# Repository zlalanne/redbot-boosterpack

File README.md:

# RedBot BoosterPack

This project is a port of Sparkfun's RedBot Mainboard to BoosterPack form to be used with TI LaunchPads + Energia

Please check the GitHub issue tracker for any known hardware/software issues

## Changes from SparkFun's RedBot Mainboard
* Removed Atmega328 and replaced with BoosterPack headers. BoosterPack should work with any 40-pin launchpad that follows the [BoosterPack pinout standard](http://www.ti.com/ww/en/launchpad/img/launchpad-byob-pinout.png)
* Removed XBee to make board cheaper, if XBee needed get another BoosterPack
* Made sizes of caps/resistors larger to make soldering easier
* Most of the logic now runs on 3.3V since the F5529 is 3.3V as well
* Removed USB connection that was using for programming device, programming is handled on the LaunchPad
* Changed layout from 4 layer to 2 layer

## Additional Hardware Support
One of the great features about the RedBot ecosystem is the number of products SparkFun has come out with that plug into the RedBot. 

The following are currently fully supported:
* [Magician Chasis (including motors)](https://www.sparkfun.com/products/10825)
* [RedBot Buzzer](https://www.sparkfun.com/products/12567)
* [RedBot Sensor - Mechanical Bumper](https://www.sparkfun.com/products/11999). Need to put instructions on wiki

The following are under development
* [RedBot Sensor - Line Follower](https://www.sparkfun.com/products/11769). Needs software support
* [RedBot Sensor - Wheel Encoder](https://www.sparkfun.com/products/12617). Needs software support
* [RedBot Sensor - Accelerometer](https://www.sparkfun.com/products/12589). Issue with v1.0 of board, needs software support

## Repository Contents
* **/Firmware/RedBot** - RedBot Energia library
* **/Hardware** - Eagle PCB layout and schematic files along with BOM

## License Information
License is inherited from [SparkFun's RedBot repository](https://github.com/sparkfun/RedBot)

All contents of this repository are released under [Creative Commons Share-alike 3.0](http://creativecommons.org/licenses/by-sa/3.0/).

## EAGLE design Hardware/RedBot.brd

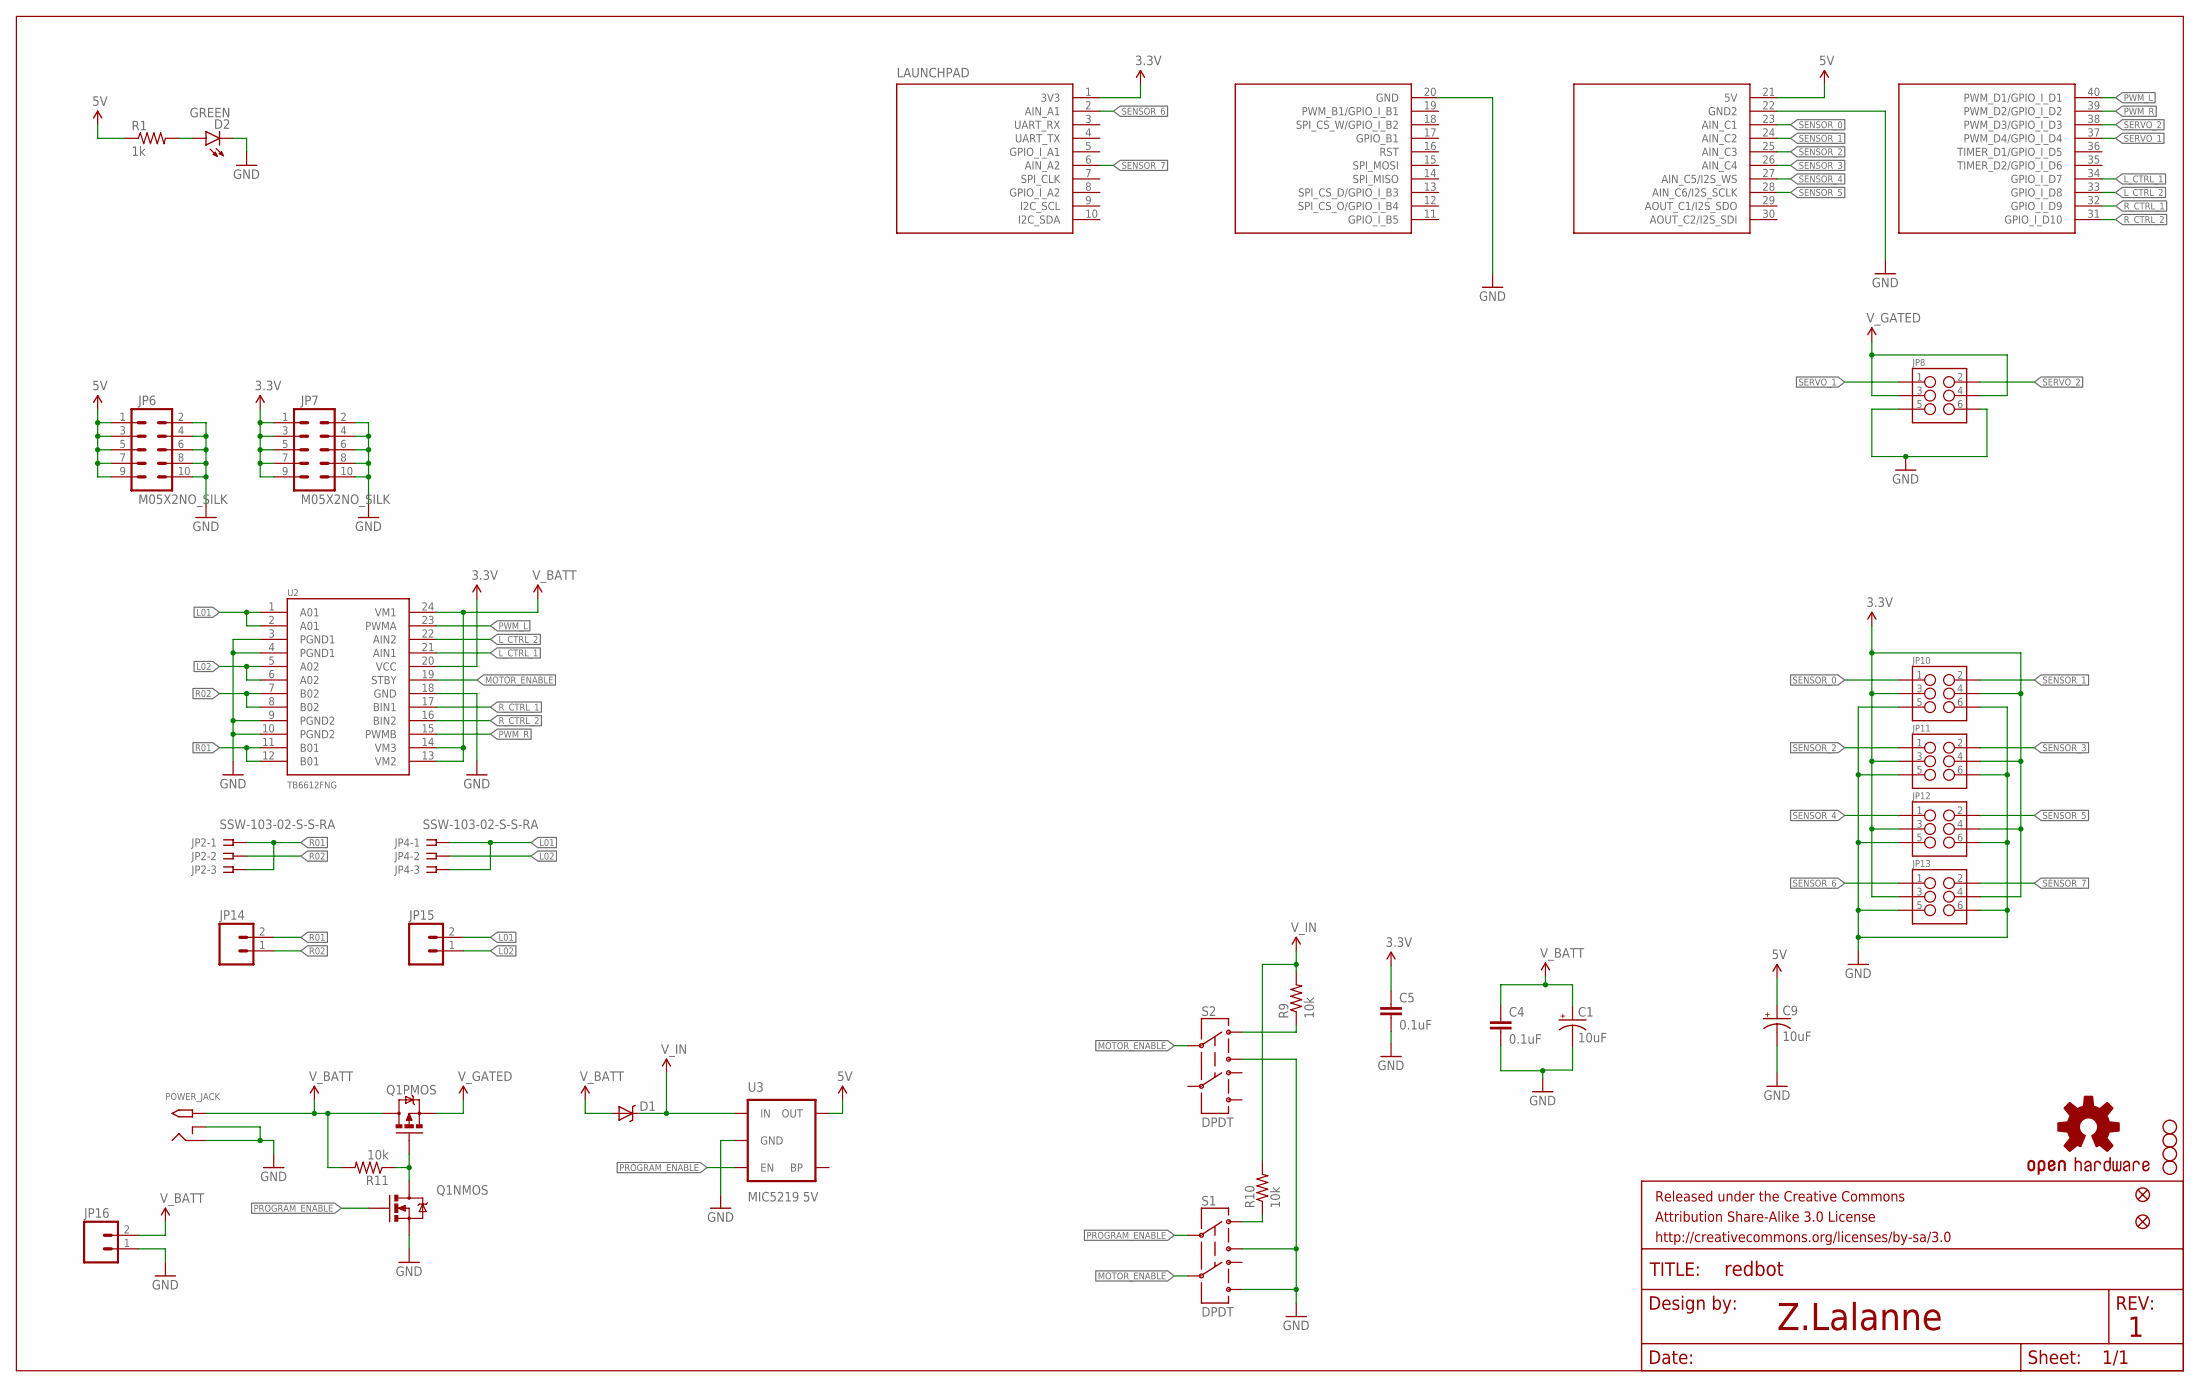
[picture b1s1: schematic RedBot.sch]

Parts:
C1, C9: 10uF; EIA3216
C4, C5: 0.1uF; 1206
D1: B340A; SMA-DIODE
D2: GREEN; LED-1206
FID1, FID2: FIDUCIALUFIDUCIAL; MICRO-FIDUCIAL
FRAME1: FRAME-LETTER; CREATIVE_COMMONS
JP2, JP4: SSW-103-02-S-S-RA
JP6, JP7: M05X2NO_SILK; 2X5_NOSILK
JP8, JP10, JP11, JP12, JP13: M03X22X3_SILK_SM; 2X3
JP14, JP15, JP16: M02PTH; 1X02
LAUNCHPAD: BOOSTERPACK; BOOSTERPACK40
POWER_JACK: 2.1MMJACKTHM; PJ-102A
Q1: IRF7509; MSOP8
R1: 1k; 1206
R9, R10, R11: 10k; 1206
S1, S2: DPDT; AYZ0202
STANDOFF1, STANDOFF2, STANDOFF3, STANDOFF4: STAND-OFF
U2: TB6612FNG; SSOP24
U3: MIC5219 5V; SOT23-5
U$17: OSHW-LOGOS; OSHW-LOGO-S

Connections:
3.3V: C5.1, JP7.1, JP7.3, JP7.5, JP7.7, JP7.9, JP10.3, JP10.4, JP11.3, JP11.4, JP12.3, JP12.4, JP13.3, JP13.4, LAUNCHPAD.1 (3V3), U2.20 (VCC)
5V: C9.A (+), JP6.1, JP6.3, JP6.5, JP6.7, JP6.9, LAUNCHPAD.21 (5V), R1.1, U3.5 (OUT)
GND: C1.C (-), C4.2, C5.2, C9.C (-), D2.C, JP6.2, JP6.4, JP6.6, JP6.8, JP6.10, JP7.2, JP7.4, JP7.6, JP7.8, JP7.10, JP8.5, JP8.6, JP10.5, JP10.6, JP11.5, JP11.6, JP12.5, JP12.6, JP13.5, JP13.6, JP16.1, LAUNCHPAD.20 (GND), LAUNCHPAD.22 (GND2), POWER_JACK.RING, POWER_JACK.RING_SW, Q1.1 (S), S1.3, S1.6, S2.3, U2.3 (PGND1), U2.4 (PGND1), U2.9 (PGND2), U2.10 (PGND2), U2.18 (GND), U3.2 (GND)
L01: JP4.1, JP4.3, JP15.2, U2.1 (A01), U2.2 (A01)
L02: JP4.2, JP15.1, U2.5 (A02), U2.6 (A02)
L_CTRL_1: LAUNCHPAD.34 (GPIO_I_D7), U2.21 (AIN1)
L_CTRL_2: LAUNCHPAD.33 (GPIO_I_D8), U2.22 (AIN2)
MOTOR_ENABLE: S1.5, S2.2, U2.19 (STBY)
unnamed: D2.A, R1.2
unnamed: Q1.4 (G), Q1.7 (D), Q1.8 (D), R11.1
unnamed: R9.1, S2.1
PG_EN: R10.1, S1.1
PROGRAM_ENABLE: Q1.2 (G), S1.2, U3.3 (EN)
PWM_L: LAUNCHPAD.40 (PWM_D1/GPIO_I_D1), U2.23 (PWMA)
PWM_R: LAUNCHPAD.39 (PWM_D2/GPIO_I_D2), U2.15 (PWMB)
R01: JP2.1, JP2.3, JP14.2, U2.11 (B01), U2.12 (B01)
R02: JP2.2, JP14.1, U2.7 (B02), U2.8 (B02)
R_CTRL_1: LAUNCHPAD.32 (GPIO_I_D9), U2.17 (BIN1)
R_CTRL_2: LAUNCHPAD.31 (GPIO_I_D10), U2.16 (BIN2)
SENSOR_0: JP10.1, LAUNCHPAD.23 (AIN_C1)
SENSOR_1: JP10.2, LAUNCHPAD.24 (AIN_C2)
SENSOR_2: JP11.1, LAUNCHPAD.25 (AIN_C3)
SENSOR_3: JP11.2, LAUNCHPAD.26 (AIN_C4)
SENSOR_4: JP12.1, LAUNCHPAD.27 (AIN_C5/I2S_WS)
SENSOR_5: JP12.2, LAUNCHPAD.28 (AIN_C6/I2S_SCLK)
SENSOR_6: JP13.1, LAUNCHPAD.2 (AIN_A1)
SENSOR_7: JP13.2, LAUNCHPAD.6 (AIN_A2)
SERVO_1: JP8.1, LAUNCHPAD.37 (PWM_D4/GPIO_I_D4)
SERVO_2: JP8.2, LAUNCHPAD.38 (PWM_D3/GPIO_I_D3)
V_BATT: C1.A (+), C4.1, D1.A, JP16.2, POWER_JACK.TIP, Q1.5 (D), Q1.6 (D), R11.2, U2.13 (VM2), U2.14 (VM3), U2.24 (VM1)
V_GATED: JP8.3, JP8.4, Q1.3 (S)
V_IN: D1.C, R9.2, R10.2, U3.1 (IN)

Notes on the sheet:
Z.Lalanne

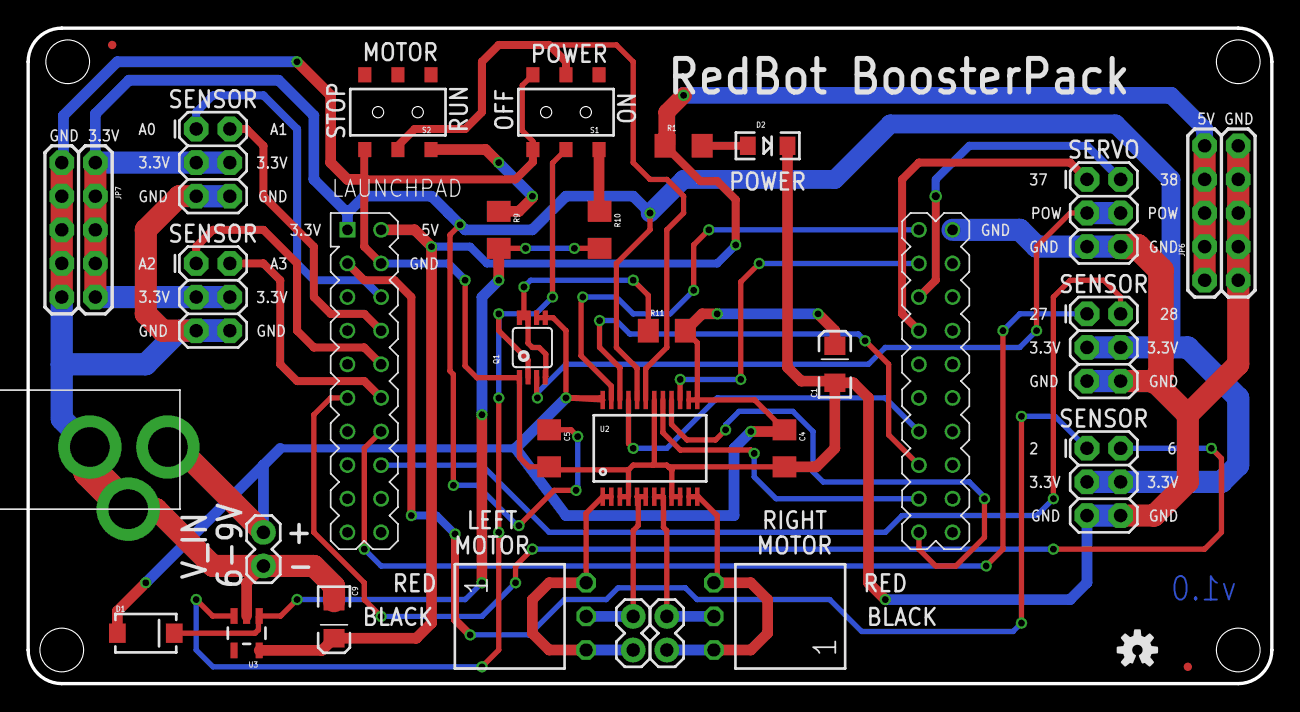
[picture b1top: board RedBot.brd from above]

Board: 2 copper layers, 94.0 x 49.5 mm, 37 parts (0 on the bottom side), 32 nets.

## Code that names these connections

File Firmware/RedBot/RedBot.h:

/****************************************************************
Core header file for all the various RedBot functions.

There is additional license info below regarding the use of the
SoftwareSerial library from Arduino 1.0.5; I had good and sound
reasons for creating a derivative class rather than asking users
to simply use the existing library, which are documented below.

This code is beerware; if you use it, please buy me (or any other
SparkFun employee) a cold beverage next time you run into one of
us at the local.

21 Jan 2014- Mike Hord, SparkFun Electronics

Code developed in Arduino 1.0.5, on an SparkFun Redbot v12.
****************************************************************/
/****************************************************************
Migrated to Energia by Zack Lalanne
****************************************************************/

#ifndef RedBot_h
#define RedBot_h

#include <Energia.h>

// Pin aliases for the motor controller.
#define    L_CTRL_1   34
#define    L_CTRL_2   33
#define    PWM_L      40

#define    R_CTRL_1   32
#define    R_CTRL_2   31
#define    PWM_R      39

// PCINT functionality aliases. Each PCINT has a value set up when the
//  class member gets created, and the PCINT service routine will handle
//  the choosing the appropriate response to the interrupt.
#define NOT_IN_USE    0
#define WHISKER       1
#define LENCODER      2
#define RENCODER      3
#define SW_SERIAL     4

#define PCINT_A0      0
#define PCINT_A1      1
#define PCINT_A2      2
#define PCINT_A3      3
#define PCINT_A4      4
#define PCINT_A5      5
#define PCINT_3       6
#define PCINT_9       7
#define PCINT_10      8
#define PCINT_11      9

enum WHEEL {LEFT, RIGHT, BOTH}; // Variable for which wheel you're interested in
                  //  when you do things in the encoder class.

// These three functions need to work from within multiple classes, so we keep
//  them separate and add them as friend functions where appropriate.
void setPinChangeInterrupt(int pin, byte role); // The "role" of each pin is
                  //  stored in an array which is accessed in the interrupt
                  //  handler to determine what should be done on a falling edge
                  //  PC interrupt.
void pinFunctionHandler(byte pinIndex); // This is the function which actually
                  //  handles the legwork after the interrupt has identified
                  //  which pin caught the interrupt.
void brake(void); // Globally accessible motor brake. I couldn't figure out how
                  //  to set a function pointer to the RedBotMotor class
                  //  function, and it's a small function, so I just made a
                  //  global in the library.
void PC0Handler(byte PBTemp);
void PC1Handler(byte PCTemp);
void PC2Handler(byte PDTemp);


// This class handles motor functionality. I expect one instance of this at the
//  start of a piece of RedBot code.
class RedBotMotor
{
  public:
    RedBotMotor();          // Constructor. Mainly sets up pins.
    void drive(int speed);  // Drive in direction given by sign, at speed given
                            //  by magnitude of the parameter.
    void pivot(int speed);  // Pivot more or less in place. Turns motors in
                            //  opposite directions. Positive values correspond
                            //  to anti-clockwise rotation.
    void rightDrive(int speed); // Drive just the left motor, as drive().
    void leftDrive(int speed);  // Drive just the right motor, as drive().
    void stop();            // Stop motors, but allow them to coast to a halt.
    void brake();           // Quick-stop the motors, shorting the leads.
    void rightStop();       // Stop right motor, as with stop().
    void leftStop();        // Stop left motor, as with stop().
    void leftBrake();       // Quick-stop left motor, as with brake().
    void rightBrake();      // Quick-stop right motor, as with brake().
  private:
    void leftFwd(byte speed); // These functions are pretty self-explanatory,
    void leftRev(byte speed); //  and are called by the above functions once
    void rightFwd(byte speed);//  sign has been used to determine direction.
    void rightRev(byte speed);
};

// This handles the physical wire-whisker type bumper.
class RedBotBumper
{
  public:
    RedBotBumper(int pin); // Simple constructor; when the bumper gets hit, the
                           //  motors will stop.
    RedBotBumper(int pin, void(*functionPointer)(void)); // If the user wishes
                           //  to do something other than stop on a whisker,
                           //  bump, they can write a function to do so, and
                           //  use this constructor.
    int pressed();        // Check if bumper is pressed
  private:
    int pin;
    void setBumpFunction(int pin, void(*functionPointer)(void));
};


#endif

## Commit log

2014-03-20 Initial import of redbot schematic/board
2014-03-25 First pass at converting schematic
2014-03-25 Updated motor ic to use 3.3V
2014-03-26 Updated parts to use through hole for sensor/servo connectors
2014-05-06 Updated board and schematic
2014-05-21 Updated board with new power jack. Started routing. Added BOM
2014-05-21 Added gitignore for temp files
2014-05-21 Removing temporary files from git
2014-05-23 Updated all parts to be larger
2014-05-23 Finished layout of RedBot
2014-05-25 Finished silk on board
2014-05-29 Added bom in csv format
2014-05-29 Removed old bom
2014-06-14 Working motors in Energia
2014-06-14 Adding some examples
2014-06-14 Added example showing how to pivot
2014-06-14 Added comments to mention port to energia
2014-06-14 Updated readme with useful information
2014-06-14 Added more info to README
2014-06-15 Updated readme with layer description
2014-06-15 Added support for RedBotBumper()
2014-06-15 Updated readme with support for bumper
2014-06-15 Cleaning up repo
2014-06-28 Made folders so that Energia recognizes examples corretly
2014-06-28 Added motor headers to BOM
2014-10-10 PlatformIO Library Manager manifest file
    PlatformIO Library Manager manifest file
    * This library in Web: http://platformio.ikravets.com/#!/lib/show/Energia-RedBot
    * Specification: [PlatformIO Library Manager](http://docs.platformio.ikravets.com/en/latest/librarymanager/index.html)
    * Integration: [IDE Integration](http://docs.platformio.ikravets.com/en/latest/ide.html)
    `library.json` is a library manifest file which can be used with different tools/managers to organise embedded libraries. Currently, only [PlatformIO](http://platformio.ikravets.com) uses it. How doe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
    ```bash
2014-10-20 Avoid trademark issues with library name
    Added frameworks and platforms fields
2014-10-23 Fix "include" field

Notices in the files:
parts and their libraries:
SparkFun-Aesthetics: Licensing: CC v3.0 Share-Alike You are welcome to use this library for commercial purposes.
SparkFun-Aesthetics: Released under the Creative Commons Attribution Share-Alike 3.0 License
SparkFun-Aesthetics: Released under the Creative Commons
